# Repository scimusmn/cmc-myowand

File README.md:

# cmc-myowand

A myoelectric sensor demonstrator, converting muscular electrical impulses into music.

## overview

There are two main subfolders here: `electronics` contains the schematics and board layouts, as well as some information on how they were designed. `code` contains two things:

 * `cinci-biomed-myo`: the Arduino sketch that processes the amplified myoelectric signals and outputs them to the computer over serial
 * `myowand-audio`: the JavaScript code to receive the Arduino's messages and conver them into musical tones.

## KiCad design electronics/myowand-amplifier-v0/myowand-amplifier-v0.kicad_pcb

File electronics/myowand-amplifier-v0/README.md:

# myowand-amplifier-v0

A prototype version of the MyoWand board. **I CANNOT EMPHASIZE ENOUGH THAT THIS BOARD IS A PROTOTYPE!** It omits several features that should be included in the final design. This board is essentially a pared-down version of the [ModularEEG amplifier board](https://openeeg.sourceforge.net/doc/modeeg/modeeg.html).

The TRS jacks connect to external [Olimex active electrodes](https://www.olimex.com/Products/EEG/Electrodes/EEG-AE/open-source-hardware) which seem to give much better signals than ordinary electrodes, especially without electrolyte solution.

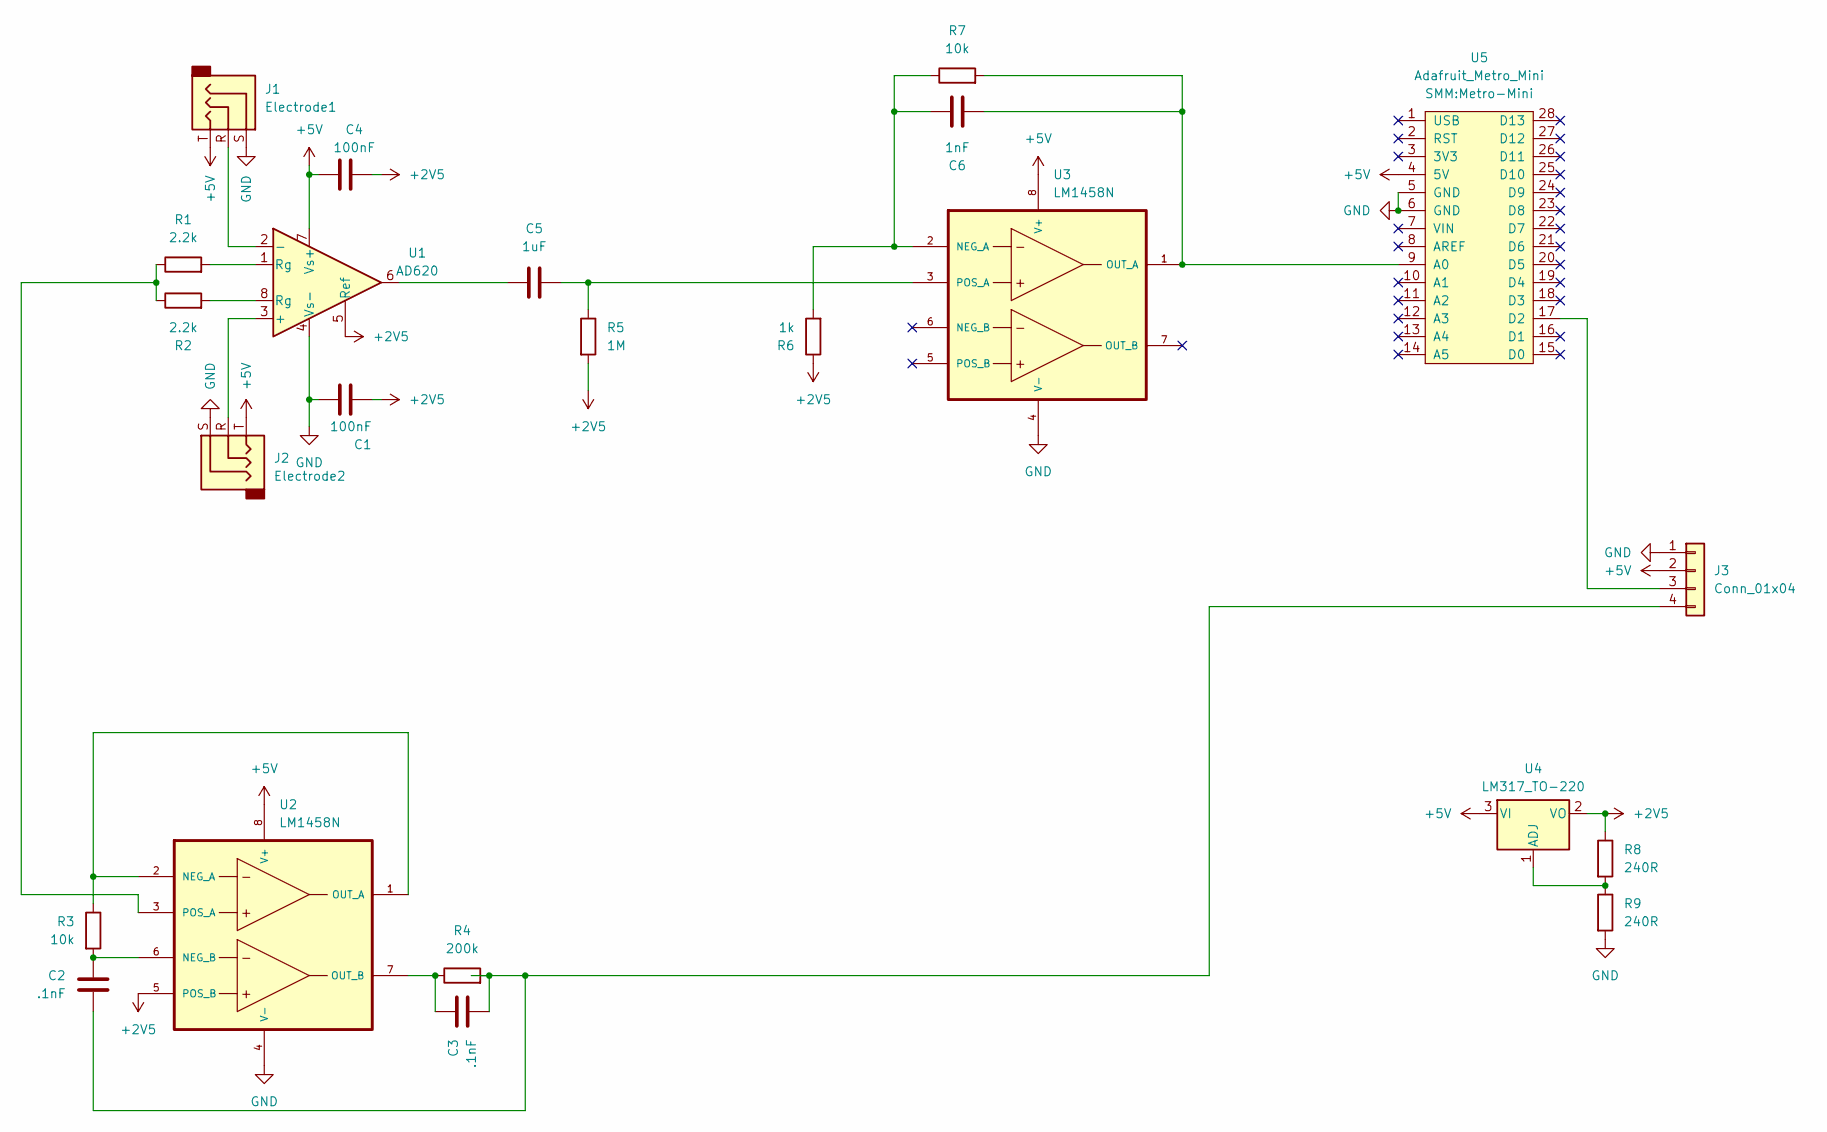
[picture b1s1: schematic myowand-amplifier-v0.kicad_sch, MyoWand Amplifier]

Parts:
C1, C4: 100nF; C_Disc_D8.0mm_W2.5mm_P5.00mm
C2, C3: .1nF; C_Disc_D8.0mm_W2.5mm_P5.00mm
C5: 1uF; C_Disc_D8.0mm_W2.5mm_P5.00mm
C6: 1nF; C_Disc_D8.0mm_W2.5mm_P5.00mm
J1: Electrode1; Jack_3.5mm_CUI_SJ1-3523N_Horizontal
J2: Electrode2; Jack_3.5mm_CUI_SJ1-3523N_Horizontal
J3: Conn_01x04; KK-1x04
R1, R2: 2.2k; Resistor_L6.3mm_D2.5mm_P10.16mm_Horizontal
R3, R7: 10k; Resistor_L6.3mm_D2.5mm_P10.16mm_Horizontal
R4: 200k; Resistor_L6.3mm_D2.5mm_P10.16mm_Horizontal
R5: 1M; Resistor_L6.3mm_D2.5mm_P10.16mm_Horizontal
R6: 1k; Resistor_L6.3mm_D2.5mm_P10.16mm_Horizontal
R8, R9: 240R; Resistor_L6.3mm_D2.5mm_P10.16mm_Horizontal
U1: AD620; DIP-8_W7.62mm_Socket
U2, U3: LM1458N; DIP-8_W7.62mm_Socket
U4: LM317_TO-220; TO-220-3_Vertical
U5: Adafruit_Metro_Mini; Metro-Mini

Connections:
+2V5: C1.1, C4.2, R5.2, R6.1, R8.1, U1.5 (Ref), U2.5 (POS_B), U4.2 (VO)
+5V: C4.1, J1.T, J2.T, J3.2, U1.7 (Vs+), U2.8 (V+), U3.8 (V+), U4.3 (VI), U5.4 (5V)
GND: C1.2, J1.S, J2.S, J3.1, R9.2, U1.4 (Vs-), U2.4 (V-), U3.4 (V-), U5.5 (GND), U5.6 (GND)
unnamed: C5.1, U1.6
unnamed: J3.3, U5.17 (D2)
unnamed: C2.2, C3.2, J3.4, R4.2
unnamed: R1.2, U1.1 (Rg)
unnamed: R2.2, U1.8 (Rg)
unnamed: J2.R, U1.3 (+)
unnamed: J1.R, U1.2 (-)
unnamed: R3.1, U2.1 (OUT_A), U2.2 (NEG_A)
unnamed: C2.1, R3.2, U2.6 (NEG_B)
unnamed: C3.1, R4.1, U2.7 (OUT_B)
unnamed: R1.1, R2.1, U2.3 (POS_A)
unnamed: C6.1, R6.2, R7.1, U3.2 (NEG_A)
unnamed: C6.2, R7.2, U3.1 (OUT_A), U5.9 (A0)
unnamed: C5.2, R5.1, U3.3 (POS_A)
unnamed: R8.2, R9.1, U4.1 (ADJ)

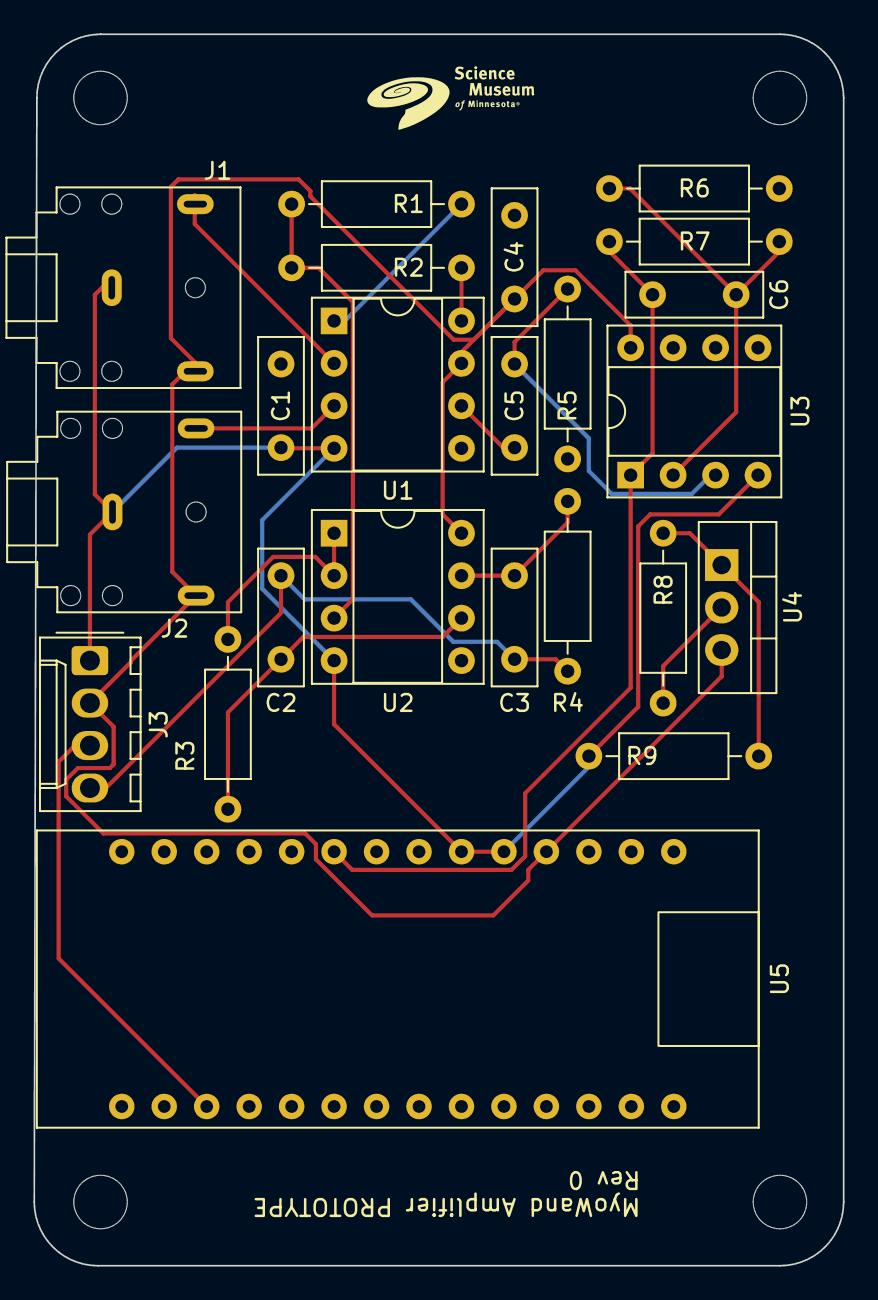
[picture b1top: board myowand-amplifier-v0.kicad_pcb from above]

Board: 2 copper layers, 48.4 x 73.7 mm, 23 parts (0 on the bottom side), 18 nets.

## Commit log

2024-01-25 move myowand-audio into current repo
2024-01-25 add plotting
